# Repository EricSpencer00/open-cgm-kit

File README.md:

# Open CGM Kit

What if you could vibe code / CAD / wet-lab a CGM? 

----------

An open glucose sensor: our own electrode, open readout electronics, and
calibration software.

**Status:** designed and software-tested. No sensor has been fabricated or has
measured glucose. Not for human use or treatment decisions.

## Path to an MVP

1. **Strip rig.** Commercial glucometer strips + LMP91000 front end + ESP32 BLE
   → calibration software. Proves the readout, firmware and calibration end to
   end without chemistry.
2. **Coated electrodes.** Contract-coated GOx electrodes built to the membrane
   spec from the model. Bench tests at air and low O2.
3. **Biocoin readout.** Port to the open UCSD [Biocoin](https://github.com/ProfDrewHall/Biocoin) board with CA gain raised
   from 10 kΩ to ≥160 kΩ.
4. **Wearable sensor.** Separate future development.

## Run

```sh
python3 models/electrode_model.py                     # electrode model -> models/out/
cd models && python3 -m unittest -v                   # model verification
RZ_BIN=/path/to/rz sh software/resilient/run_checks.sh   # calibration core
RZ_BIN=/path/to/rz python3 -m unittest discover -s software/bridge -v
```

## Layout

| Path | Contents |
| --- | --- |
| `models/` | Electrode reaction-diffusion model, membrane spec, readout resolution |
| `software/` | Resilient calibration core and Biocoin BLE bridge |
| `hardware/`, `mechanical/` | A0 electrode masks, enclosure and pad CAD |
| `hardware/ock_p1/` | OCK-P1 pod board: 22 × 18 mm, glucose-only Biocoin derivative (KiCad) |
| `mechanical/product_B1.py` | B1 product: reusable pod, disposable base and patch (STL, render) |
| `docs/index.html` | Landing page with live 3D viewer (GitHub Pages from `/docs`) |
| `vendor/biocoin/` | Upstream [Biocoin](https://github.com/ProfDrewHall/Biocoin) readout (PCB, firmware, host), pinned and hashed |
| `docs/A0_PACKAGE.md` | Full A0 package: contents, delivered box, Bluetooth, provenance |
| `docs/SENSOR_PROCESS.md` | Sensor chemistry, layer stack, bench test gates |
| `docs/RELEASE_STATUS.md` | What is verified and what remains |
| `docs/FABRICATION.md`, `docs/COST_AND_BOX.md` | Supplier handoff and cost |
| `docs/OPEN_HARDWARE_CATALOG.md` | Survey of open CGM hardware and software |

## License

Hardware CERN-OHL-W-2.0, software MIT, docs CC-BY-4.0. Biocoin keeps its
upstream licenses. See `LICENSES/` and `docs/ATTRIBUTION.md`.

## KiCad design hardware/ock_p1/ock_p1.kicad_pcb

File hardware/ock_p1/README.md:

# OCK-P1 pod board

A glucose-only derivative of [Biocoin v1.3](https://github.com/ProfDrewHall/Biocoin), sized for the B1 pod (`mechanical/product_B1.py`).

| | Biocoin v1.3 | OCK-P1 |
| --- | --- | --- |
| Board | 26 mm round, 6 layers, 0.94 mm | 22 × 18 mm, 6 layers HDI, 0.8 mm |
| Radio/MCU | MDBT50Q (nRF52840), 10 × 15.5 × 2.2 mm | ISP1807 (nRF52840 SiP, antenna inside), 8 × 8 × 1 mm |
| Analog front end | AD5940 + 4:1 mux, pH buffers, iontophoresis, strain/temp | AD5940 only, WE/RE/CE direct |
| Power | MAX17270 buck-boost, 110 mAh coin cell | TPS7A0230 LDO, bq25100 charger, ~12 mAh 2 mm pouch |
| Sensor interface | 20-pin ZIF (10 mating cycles) | 3 ENIG spring-contact pads |
| Dock interface | Pogo pads | VBUS, GND, SWDIO, SWDCLK pads |
| Pod | 36 × 31 × 8.5 mm | 27.6 × 23.4 × 6.0 mm |

**What carries over unchanged:**
- **AD5940 circuit:** every ball-to-net connection and decoupling value is copied from the pinned Biocoin layout and schematic.
- **Firmware:** the nRF52840 port pins are the same: SPI on P0.13/14/15, CS P0.04, interrupt P0.05, reset P0.02, AFE power P0.26 (active low through the same dual P-FET), battery divider P0.29, LED P0.20. Biocoin firmware, or the patched build in `firmware/biocoin-patches`, should run without a new variant. Pins for parts that were removed drive nothing.

## Power

`python3 power_budget.py [cell_mAh]` adds up datasheet currents:

| Load | µA |
| --- | ---: |
| AD5940 low-power potentiostat loop, continuous | 8.5 |
| AD5940 ADC, 50 ms burst every 30 s | 3.4 |
| nRF52840 idle with RTC | 3.0 |
| BLE events and notifications | 1.6 |
| Divider, buffer, LDO, charger leakage, LED | 1.2 |
| **Total** | **17.7** |

That is about 6.4 mAh per 15-day wear, or about 23 days per charge on a 12 mAh cell. The BLE energy per event is an estimate; measure it on hardware.

## Build

```sh
./make.sh        # needs KiCad 10; imports Biocoin, regenerates footprints, board, DRC, renders
```

`build_board.py` holds the netlist and placement; it is the design source (no schematic yet). `ock_p1.pretty` contains footprints extracted from the Biocoin layout (AD5940 CB-56-3, CSD75208 dual P-FET, MAX44264, ferrite) plus the ISP1807 land pattern built from its datasheet drawing.

## Status

| Step | State |
| --- | --- |
| Netlist, placement, antenna keep-out, via-in-pad escapes | Done |
| DRC (errors) on the placed board | 0 violations, 106 unrouted connections |
| Routing | Not done. `route_board.py` drives Freerouting; running it needs approval for the downloaded jar |
| Post-route DRC, Gerbers, drill, pick-and-place | Not done |
| Schematic | Not done; netlist lives in `build_board.py` |

Open items before fabrication:
- **CLPF value:** Biocoin's schematic gives no value for its LPF0 capacitor; 1 µF is a placeholder.
- **ISP1807 land pattern:** positions were measured from the R19 drawing to about ±0.02 mm. Check them against Insight SiP's CAD files.
- **Antenna:** the 4.3 mm keep-out follows the datasheet. The pod plastic and the patient's body will detune it; measure range on hardware.
- **Unprotected interfaces:** VBUS and SWD contact pads have no ESD protection, and WE/RE/CE have no guard ring.
- **Shipping mode:** with no button or ship mode, a stored pod draws about 2 µA.
- **Dock:** needs a new fixture for the bottom pads.

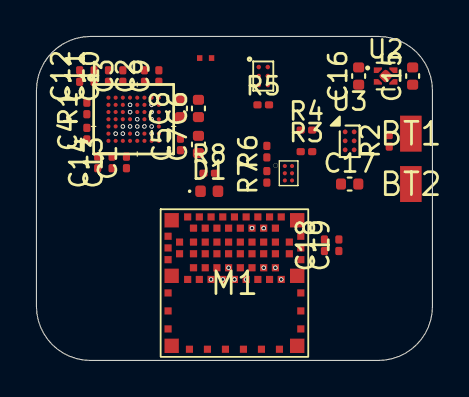
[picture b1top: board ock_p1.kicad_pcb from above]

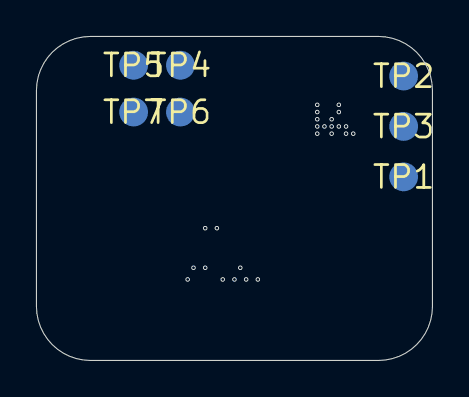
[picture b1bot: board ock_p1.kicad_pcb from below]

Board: 6 copper layers, 22.0 x 18.0 mm, 44 parts (7 on the bottom side), 38 nets, no tracks yet.

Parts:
BT1: VBAT; BatteryTab_1.2x2.0mm
BT2: GND; BatteryTab_1.2x2.0mm
C1, C2, C4, C5: 470nF; C_0201_0603Metric
C3, C10, C13, C18: 4.7uF; C_0201_0603Metric
C6, C7: 100nF; C_0402_1005Metric
C8: 33nF; C_0402_1005Metric
C9: 1uF; C_0201_0603Metric
C11, C12, C14, C19: 100nF; C_0201_0603Metric
C15, C16: 4.7uF; C_0402_1005Metric
C17: 1uF; C_0402_1005Metric
D1: APHHS1005LCGCK; LED_0402_1005Metric
FB1: MMZ0603S601HT000; 0201 FERRITE
M1: ISP1807-LR; InsightSiP_ISP1807_LGA-78_8x8mm
Q1: CSD75208W1015; BGA6C50P2X3_145X95X62
R1: 10k 0.1%; R_0201_0603Metric
R2: 9.09k; R_0201_0603Metric
R3: 6.04k; R_0201_0603Metric
R4: 10k; R_0201_0603Metric
R5, R6: 10M; R_0201_0603Metric
R7: 4.99M; R_0201_0603Metric
R8: 5.1k; R_0201_0603Metric
TP1: WE; ContactPad_D1.6mm
TP2: RE; ContactPad_D1.6mm
TP3: CE; ContactPad_D1.6mm
TP4: VBUS; ContactPad_D1.6mm
TP5: GND; ContactPad_D1.6mm
TP6: SWDIO; ContactPad_D1.6mm
TP7: SWDCLK; ContactPad_D1.6mm
U1: AD5940BCBZ; CB-56-3_ADI
U2: TPS7A0230PDQNR; Texas_X2SON-4_1x1mm_P0.65mm
U3: BQ25100YFPR; Texas_DSBGA-6_0.9x1.4mm_Layout2x3_P0.5mm
U4: MAX44264EWT+T; 21-0217D_W61B1-1_MXM

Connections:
AFE_AVDD: C10.1, C11.1, C12.1, FB1.2, U1.A4, U1.F2
AFE_INT: M1.36, U1.F5
AFE_RESET: M1.40, U1.F1
AFE_VDD: C13.1, C14.1, FB1.1, Q1.C2, U1.F3, U1.G2
AFE_VDD_CTRL: M1.6, Q1.C1, R5.1
ANT: M1.20, M1.22
AVDD_REG: C5.1, U1.D8
CE: TP3.1, U1.A7
DVDD_REG_1V8: C1.1, U1.G3
GND: BT2.1, C1.2, C2.2, C3.2, C4.2, C5.2, C6.2, C7.2, C9.2, C10.2, C11.2, C12.2, C13.2, C14.2, C15.2, C16.2, C17.2, C18.2, C19.2, D1.1, M1.1, M1.7, M1.14, M1.16, M1.18, M1.21, M1.23, M1.24, M1.25, M1.31, R2.2, R3.2, R4.2, R7.2, TP5.1, U1.C4, U1.D5, U1.E3, U1.E4, U1.E5, U1.E6, U2.2, U2.5, U3.C2, U4.A2
ISET: R2.1, U3.B2
LED: M1.15, R8.1
LED_A: D1.2, R8.2
LPF0: C9.1, U1.B4
PRETERM: R3.1, U3.C1
RC0_0: C8.1, U1.C8
RC0_1: C8.2, U1.B8
RCAL0: R1.2, U1.C1
RCAL1: R1.1, U1.B1
RE: TP2.1, U1.A8
SPI_CS: M1.35, U1.F7
SPI_MISO: M1.37, U1.E8
SPI_MOSI: M1.29, U1.E7
SPI_SCK: M1.5, U1.F8
SWDCLK: M1.30, TP7.1
SWDIO: M1.28, TP6.1
TS: R4.1, U3.B1
VBAT: BT1.1, C15.1, R6.1, U2.3, U2.4, U3.A1
VBIAS0: C7.1, U1.C7
VBIAS_CAP: C4.1, U1.D1
VBUS: C17.1, M1.12, TP4.1, U3.A2
VDD: C16.1, C18.1, C19.1, M1.26, Q1.A2, Q1.B1, Q1.B2, R5.2, U2.1, U4.B2
VDIV: M1.46, U4.B1, U4.C1
VDIV_RAW: R6.2, R7.1, U4.A1
VREF_1V8: C3.1, U1.A5
VREF_2V5: C2.1, U1.D7
VZERO0: C6.1, U1.B7
WE: TP1.1, U1.A6

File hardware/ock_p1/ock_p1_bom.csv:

ref,value,footprint,x_mm,y_mm,side
U1,AD5940BCBZ,@U1,-5.6,-4.4,F
M1,ISP1807-LR,@M1,0.0,4.7,F
U2,TPS7A0230PDQNR,Texas_X2SON-4_1x1mm_P0.65mm,8.4,-6.8,F
Q1,CSD75208W1015,@Q1,1.6,-6.8,F
U3,BQ25100YFPR,Texas_DSBGA-6_0.9x1.4mm_Layout2x3_P0.5mm,6.4,-3.2,F
U4,MAX44264EWT+T,@U8,3.0,-1.4,F
FB1,MMZ0603S601HT000,@L4,-1.6,-7.8,F
C3,4.7uF,C_0201_0603Metric,-6.199999999999999,-6.800000000000001,F
C10,4.7uF,C_0201_0603Metric,-7.0,-6.800000000000001,F
C11,100nF,C_0201_0603Metric,-7.8,-6.800000000000001,F
C12,100nF,C_0201_0603Metric,-8.6,-6.800000000000001,F
R1,10k 0.1%,R_0201_0603Metric,-8.2,-5.0,F
C4,470nF,C_0201_0603Metric,-8.2,-3.6000000000000005,F
C8,33nF,C_0402_1005Metric,-2.9999999999999996,-5.0,F
C5,470nF,C_0201_0603Metric,-2.9999999999999996,-3.0000000000000004,F
C6,100nF,C_0402_1005Metric,-1.9999999999999996,-5.0,F
C7,100nF,C_0402_1005Metric,-1.9999999999999996,-3.0000000000000004,F
C2,470nF,C_0201_0603Metric,-5.0,-6.800000000000001,F
C9,1uF,C_0201_0603Metric,-4.199999999999999,-6.800000000000001,F
C13,4.7uF,C_0201_0603Metric,-6.8,-2.0000000000000004,F
C14,100nF,C_0201_0603Metric,-7.6,-2.0000000000000004,F
C1,470nF,C_0201_0603Metric,-6.0,-2.0000000000000004,F
C15,4.7uF,C_0402_1005Metric,9.9,-6.8,F
C16,4.7uF,C_0402_1005Metric,6.9,-6.8,F
C17,1uF,C_0402_1005Metric,6.4,-0.8,F
R2,9.09k,R_0201_0603Metric,8.6,-3.2,F
R3,6.04k,R_0201_0603Metric,4.0,-2.6,F
R4,10k,R_0201_0603Metric,4.0,-3.8,F
R5,10M,R_0201_0603Metric,1.6,-5.2,F
R6,10M,R_0201_0603Metric,1.8,-2.6,F
R7,4.99M,R_0201_0603Metric,1.8,-1.2,F
C18,4.7uF,C_0201_0603Metric,5.0,2.6,F
C19,100nF,C_0201_0603Metric,5.8,2.6,F
D1,APHHS1005LCGCK,LED_0402_1005Metric,-1.4,-0.4,F
R8,5.1k,R_0201_0603Metric,-1.4,-1.4,F
BT1,VBAT,BatteryTab_1.2x2.0mm,9.8,-3.6,F
BT2,GND,BatteryTab_1.2x2.0mm,9.8,-0.8,F
TP1,WE,ContactPad_D1.6mm,-9.4,-1.2,B
TP2,RE,ContactPad_D1.6mm,-9.4,-6.8,B
TP3,CE,ContactPad_D1.6mm,-9.4,-4.0,B
TP4,VBUS,ContactPad_D1.6mm,3.0,-7.4,B
TP5,GND,ContactPad_D1.6mm,5.6,-7.4,B
TP6,SWDIO,ContactPad_D1.6mm,3.0,-4.8,B
TP7,SWDCLK,ContactPad_D1.6mm,5.6,-4.8,B

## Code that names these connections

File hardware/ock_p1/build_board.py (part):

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    "29": "SPI_MOSI",       # P0.13
    "37": "SPI_MISO",       # P0.15
    "5": "SPI_SCK",         # P0.14
    "35": "SPI_CS",         # P0.04  PIN_SPI_CS (D14)
    "36": "AFE_INT",        # P0.05  PIN_AFE_IntPin_GPIO0 (D15)
    "40": "AFE_RESET",      # P0.02  PIN_AFE_RESET (D18)
    "6": "AFE_VDD_CTRL",    # P0.26  PIN_AFE_VDD_CTRL (D9), active low
    "46": "VDIV",           # P0.29  PIN_VDIV (D20, AIN5)
    "15": "LED",            # P0.20  PIN_LED (D28)
}

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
